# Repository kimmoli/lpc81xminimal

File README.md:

LPC81X Minimal
==============

[]

[]

BOM:

R1,R2 0603 1k00..5k00 (pull-ups)

R3 0603 300..1k00 (for the led)

H1 0603 SMD LED, green or red

C1 0603 100n

D1 LPC811 and LPC812 TSOP16

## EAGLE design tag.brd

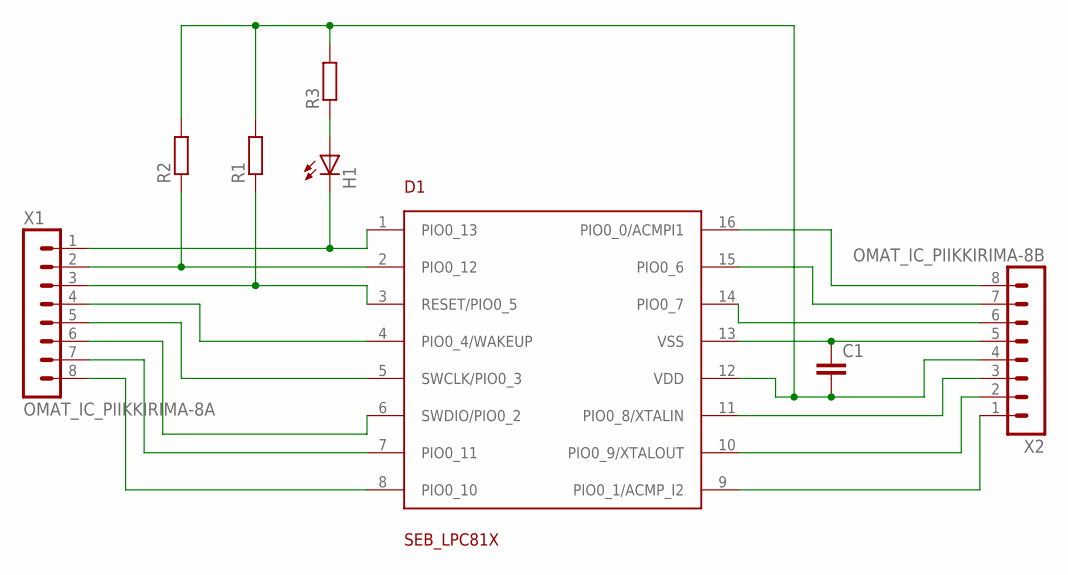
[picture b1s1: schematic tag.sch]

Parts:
C1: RCL_C-EUC0603; RCL_C0603
D1: SEB_LPC81X; SEB_TSSOP16
H1: OMAT_IC_LEDCHIP-LED0603; OMAT_IC_CHIP-LED0603
R1, R2, R3: RCL_R-EU_R0603; RCL_R0603
X1: OMAT_IC_PIIKKIRIMA-8A; OMAT_IC_PIIKKIRIMA-8
X2: OMAT_IC_PIIKKIRIMA-8B; OMAT_IC_PIIKKIRIMA-8_2

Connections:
+3V3: C1.2, D1.12 (VDD), R1.2, R2.2, R3.2, X2.4
GND: C1.1, D1.13 (VSS), X2.5
unnamed: D1.8 (PIO0_10), X1.8
unnamed: D1.7 (PIO0_11), X1.7
unnamed: D1.6 (SWDIO/PIO0_2), X1.6
unnamed: D1.5 (SWCLK/PIO0_3), X1.5
unnamed: D1.4 (PIO0_4/WAKEUP), X1.4
unnamed: D1.3 (RESET/PIO0_5), R1.1, X1.3
unnamed: D1.2 (PIO0_12), R2.1, X1.2
unnamed: D1.1 (PIO0_13), H1.C, X1.1
unnamed: H1.A, R3.1
unnamed: D1.9 (PIO0_1/ACMP_I2), X2.1
unnamed: D1.10 (PIO0_9/XTALOUT), X2.2
unnamed: D1.11 (PIO0_8/XTALIN), X2.3
unnamed: D1.14 (PIO0_7), X2.6
unnamed: D1.15 (PIO0_6), X2.7
unnamed: D1.16 (PIO0_0/ACMPI1), X2.8

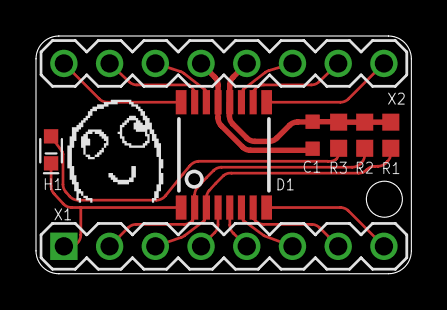
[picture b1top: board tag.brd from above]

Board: 2 copper layers, 20.9 x 13.2 mm, 9 parts (0 on the bottom side), 17 nets.

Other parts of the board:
U$1: DAFUG

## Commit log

2013-09-10 Rounding done... Finished
2013-09-10 Tuning
    Added readme
    Hole reduced to 2mm
    Bottom label to have mask opening too
2013-09-27 VCC/GND Fixed
2015-10-16 Add human readable schematic, add bom
    Fixes #1
